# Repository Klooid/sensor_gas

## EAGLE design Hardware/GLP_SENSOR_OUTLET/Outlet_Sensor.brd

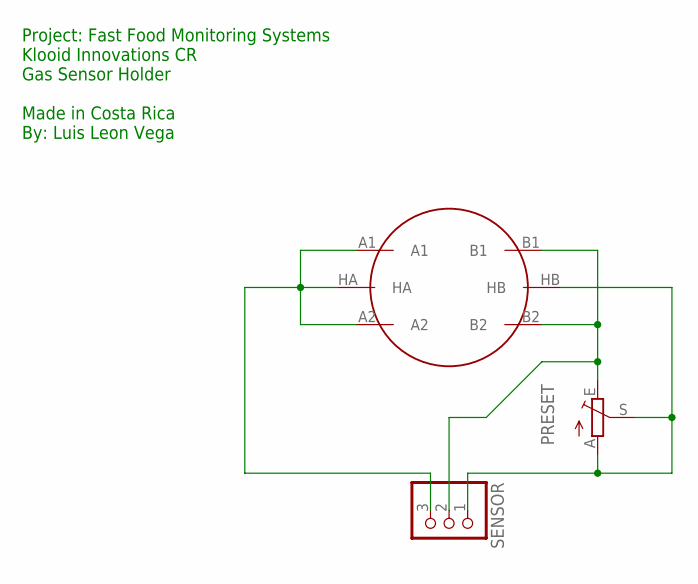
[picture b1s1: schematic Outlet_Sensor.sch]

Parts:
PRESET: TRIM_EU-B25P; B25P
SENSOR: PINHD-1X3; 1X03
U$1: METHANE_SENSOR; MQ-3

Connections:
GND: PRESET.A, PRESET.S, SENSOR.1, U$1.HB
unnamed: SENSOR.3, U$1.A1, U$1.A2, U$1.HA
unnamed: PRESET.E, SENSOR.2, U$1.B1, U$1.B2

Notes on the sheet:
Project: Fast Food Monitoring Systems Klooid Innovations CR Gas Sensor Holder Made in Costa Rica By: Luis Leon Vega

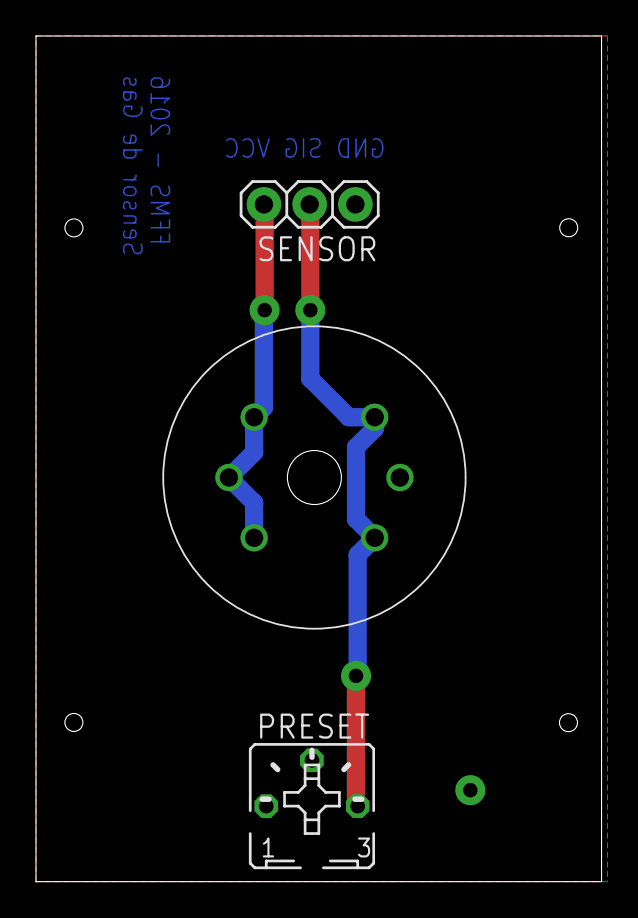
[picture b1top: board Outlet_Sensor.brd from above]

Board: 2 copper layers, 31.4 x 47.0 mm, 3 parts (0 on the bottom side), 3 nets.

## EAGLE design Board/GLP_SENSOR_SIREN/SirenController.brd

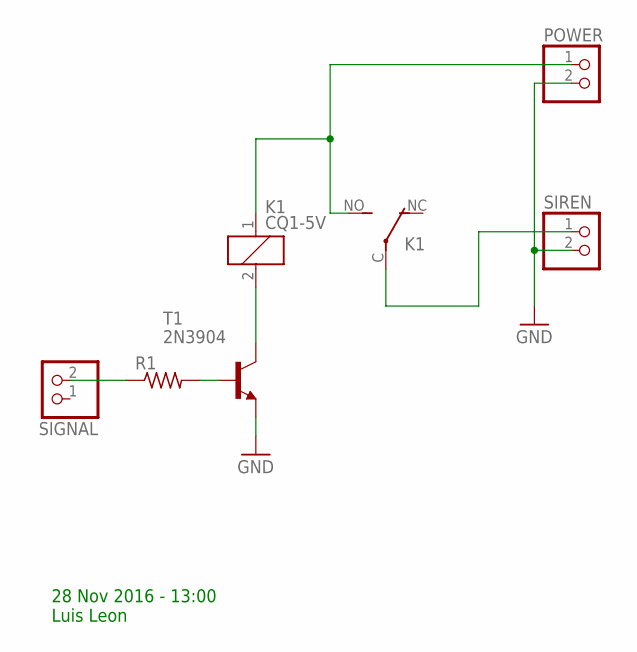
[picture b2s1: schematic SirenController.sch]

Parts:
K1: CQ1-5V; CQ1
POWER: PINHD-1X2; 1X02
R1: R-US_0309/10; 0309/10
SIGNAL: PINHD-1X2; 1X02
SIREN: PINHD-1X2; 1X02
T1: 2N3904; TO92

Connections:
GND: POWER.2, SIREN.2, T1.3 (E)
unnamed: K1.C, SIREN.1
unnamed: K1.1, K1.NO (S), POWER.1
unnamed: K1.2, T1.1 (C)
unnamed: R1.1, SIGNAL.2
unnamed: R1.2, T1.2 (B)

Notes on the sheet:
28 Nov 2016 - 13:00 Luis Leon

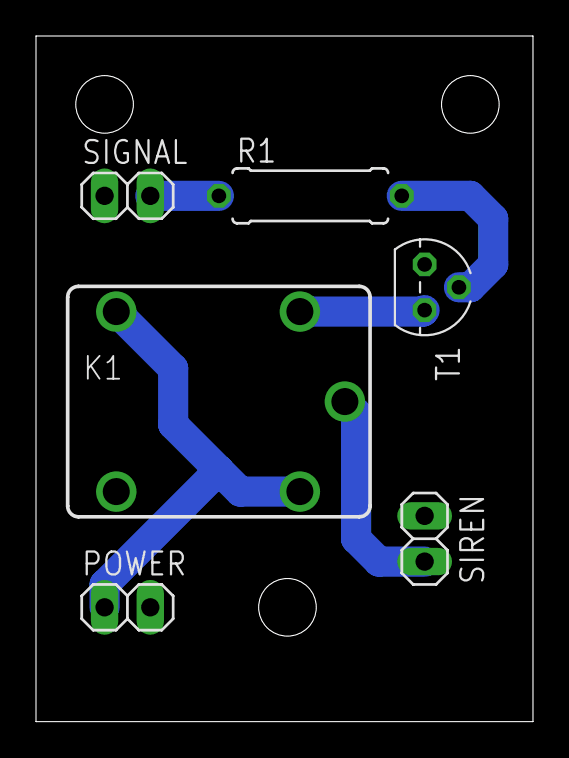
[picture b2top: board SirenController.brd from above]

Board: 2 copper layers, 27.6 x 38.1 mm, 6 parts (0 on the bottom side), 6 nets.

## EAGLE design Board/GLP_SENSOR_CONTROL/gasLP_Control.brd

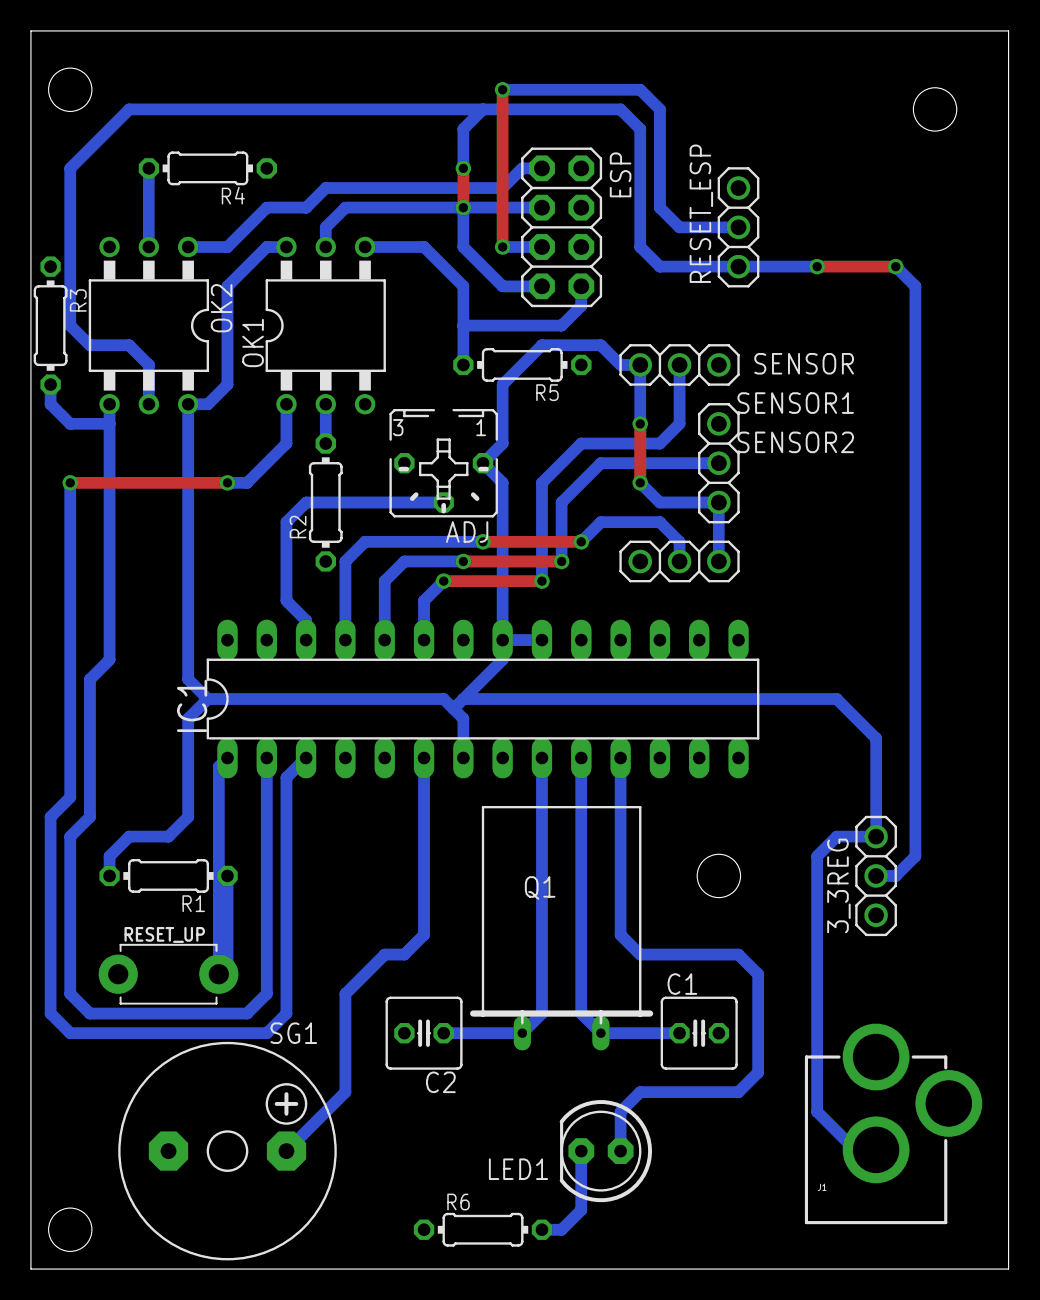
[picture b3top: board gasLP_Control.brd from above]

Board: 2 copper layers, 63.2 x 80.0 mm, 23 parts (0 on the bottom side), 20 nets.

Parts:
3_3REG: 1X03
ADJ: B25P
C1, C2: C025-050X050
ESP: 2X04
IC1: ATMEGA168-20P; DIL28-3
J1: POWER_JACKPTH; POWER_JACK_PTH
LED1: LED5MM
OK1, OK2: H11L1MT; DIL6-04
Q1: 16MHz; Q
R1, R2, R4, R6: 1K; 0204/7
R3, R5: 2.2K; 0204/7
RESET_ESP: 1X03
RESET_UP: TACT_PANA-EVQ
SENSOR, SENSOR1, SENSOR2: 1X03
SG1: F/CM12P

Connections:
+3V3: 3_3REG.2, ESP.3, ESP.7, OK1.5, OK2.5, RESET_ESP.1
GND: 3_3REG.1, ADJ.E, C1.2, C2.2, ESP.2, IC1.8, IC1.22, J1.PWR, R2.1, R3.1, R4.1, R5.1, R6.1, RESET_ESP.3, RESET_UP.P$1, SENSOR.1, SENSOR1.1, SENSOR2.1, SG1.-
unnamed: C1.1, IC1.10, Q1.2
unnamed: C2.1, IC1.9, Q1.1
unnamed: IC1.3, OK1.1
unnamed: OK1.2, R2.2
unnamed: IC1.1, R1.1, RESET_UP.P$2
unnamed: IC1.2, OK2.4, R3.2
unnamed: IC1.6, SG1.+
unnamed: OK2.2, R4.2
unnamed: ESP.8, OK1.4, R5.2
unnamed: ESP.1, OK2.1
unnamed: ESP.5, RESET_ESP.2
unnamed: IC1.11, LED1.A
unnamed: LED1.K, R6.2
unnamed: IC1.23, SENSOR.2
unnamed: ADJ.S, IC1.26
unnamed: IC1.24, SENSOR1.2
unnamed: IC1.25, SENSOR2.2
VCC: 3_3REG.3, ADJ.A, IC1.7, IC1.20, IC1.21, J1.GND, OK1.6, OK2.6, R1.2, SENSOR.3, SENSOR1.3, SENSOR2.3

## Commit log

2016-11-05 Sistema Basic
2016-11-11 añadir control
2016-11-11 Añadir el Outlet Sensor
2016-11-11 Corregir error
2016-11-30 actualizar códigos
2016-12-03 Update - Adding 3D designs
2016-12-12 Bugs solution
2016-12-12 Add SIM900 cmds
2016-12-12 Testing SMS Server Initialization
2016-12-12 Test message
2016-12-12 Add comments
2016-12-12 Send SMS routine Working
2016-12-12 Write header
2016-12-12 Again
2016-12-13 Add MySQL Service
2016-12-14 Implementing Escapes
2016-12-14 Adding Basic
2016-12-14 Delete
2017-03-13 Diseños 3D

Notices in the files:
parts and their libraries:
SparkFun-Connectors: Licensing: Creative Commons ShareAlike 4.0 International - https://creativecommons.org/licenses/by-sa/4.0
